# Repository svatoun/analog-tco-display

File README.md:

# analog-tco-display

Projekt se skládá z 2 částí: Analogové TCO a Zobrazovač obsazení

## Analogové TCO
**TCO je ovladač ANALOGOVÉHO kolejiště do ovládacího pultu**, pracuje s tlačítky (spínači) nebo přepínači. Čte stav tlačítek, sleduje změny a pomocí sběrnice RS485 odesílá jednotlivým výkonným zařízením pod kolejištěm. Sběrnice nahrazuje samostatné spínací / povelové vodiče vedoucí z pultu k jednotlivým servům, přestavníkům apod. TCO si vystačí se 3 vodiči (U+, U- a GND) a dokáže po nich přenést velké libovolné množství povelů.

Bežné "analogově řízené" kolejiště využívá jednoduchého spínání, tedy na každé zařízení (přestavník, lampa, světlo návěstidla atd) padne jeden vodič. Jejich množství může lehce vyčerpat vodiče v kabelu propojující ovládací panel s kolejištěm.

**POZOR** jedná se o ovládání ANALOGOVÉHO kolejiště, u digitálního kolejiště pomocí _XPressNet_ je pro komunikaci s centrálou použitá sicestejná kabeláž ale **jiný, standardizovaný, protokol** ! Komunikace a možnosti tohoto "analogového TCO" v žádném případě nedosahuje robustnosti a šíře protokolu XpressNet nebo LocoNet.

TCO se **konfiguruje** pomocí integrovaného USB portu v Arduinu, zapojeného do PC. 

Více viz [Analogové TCO](http://cs.ttodbocna.wikia.com/wiki/Analog_TCO)

## Zobrazení obsazení
Skládá se z několika částí:
- Proudové detektory obsazení uzpůsobené pro analogový provoz
- Enkodér detektorů pro sběrnici S88 (stejná jako se používá u digitalních kolejišť)
- Zobrazovací jednotka v ovládacím pultu
Umožňuje přenášet až 128 detekovaných úseků a zobrazovat jejich stav na ovládacím pultu. Umožňuje také do přenášených dat zapojit jiný tzp detektorů, 
např. jazýčková relé, optické senzory atd. 

Podrobnější popis bude doplněn.

## Celková "architektura"
Jak spolu spolupracují TCO, Display, proudove detektory atd atd je [vysvětleno ve Wiki](http://cs.ttodbocna.wikia.com/wiki/Architektura_Analog)

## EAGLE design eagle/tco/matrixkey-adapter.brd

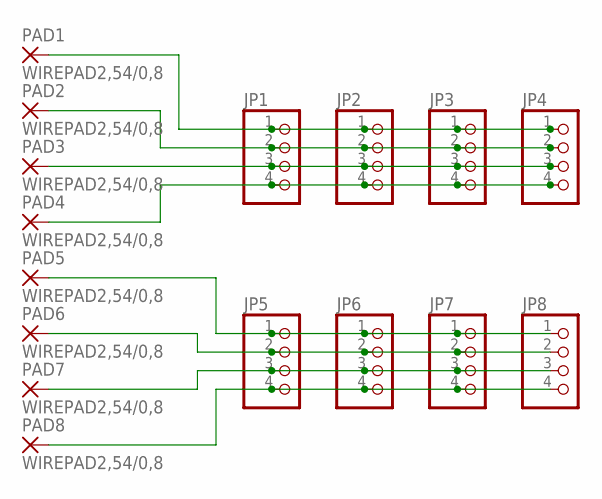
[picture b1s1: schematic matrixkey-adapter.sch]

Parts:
JP1, JP2, JP3, JP4, JP5, JP6, JP7, JP8: PINHD-1X4; 1X04
PAD1, PAD2, PAD3, PAD4, PAD5, PAD6, PAD7, PAD8: WIREPAD2,54/0,8; 2,54/0,8

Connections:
unnamed: JP1.1, JP2.1, JP3.1, JP4.1, PAD1.1
unnamed: JP1.2, JP2.2, JP3.2, JP4.2, PAD2.1
unnamed: JP1.3, JP2.3, JP3.3, JP4.3, PAD3.1
unnamed: JP1.4, JP2.4, JP3.4, JP4.4, PAD4.1
unnamed: JP5.1, JP6.1, JP7.1, JP8.1, PAD5.1
unnamed: JP5.2, JP6.2, JP7.2, JP8.2, PAD6.1
unnamed: JP5.3, JP6.3, JP7.3, JP8.3, PAD7.1
unnamed: JP5.4, JP6.4, JP7.4, JP8.4, PAD8.1

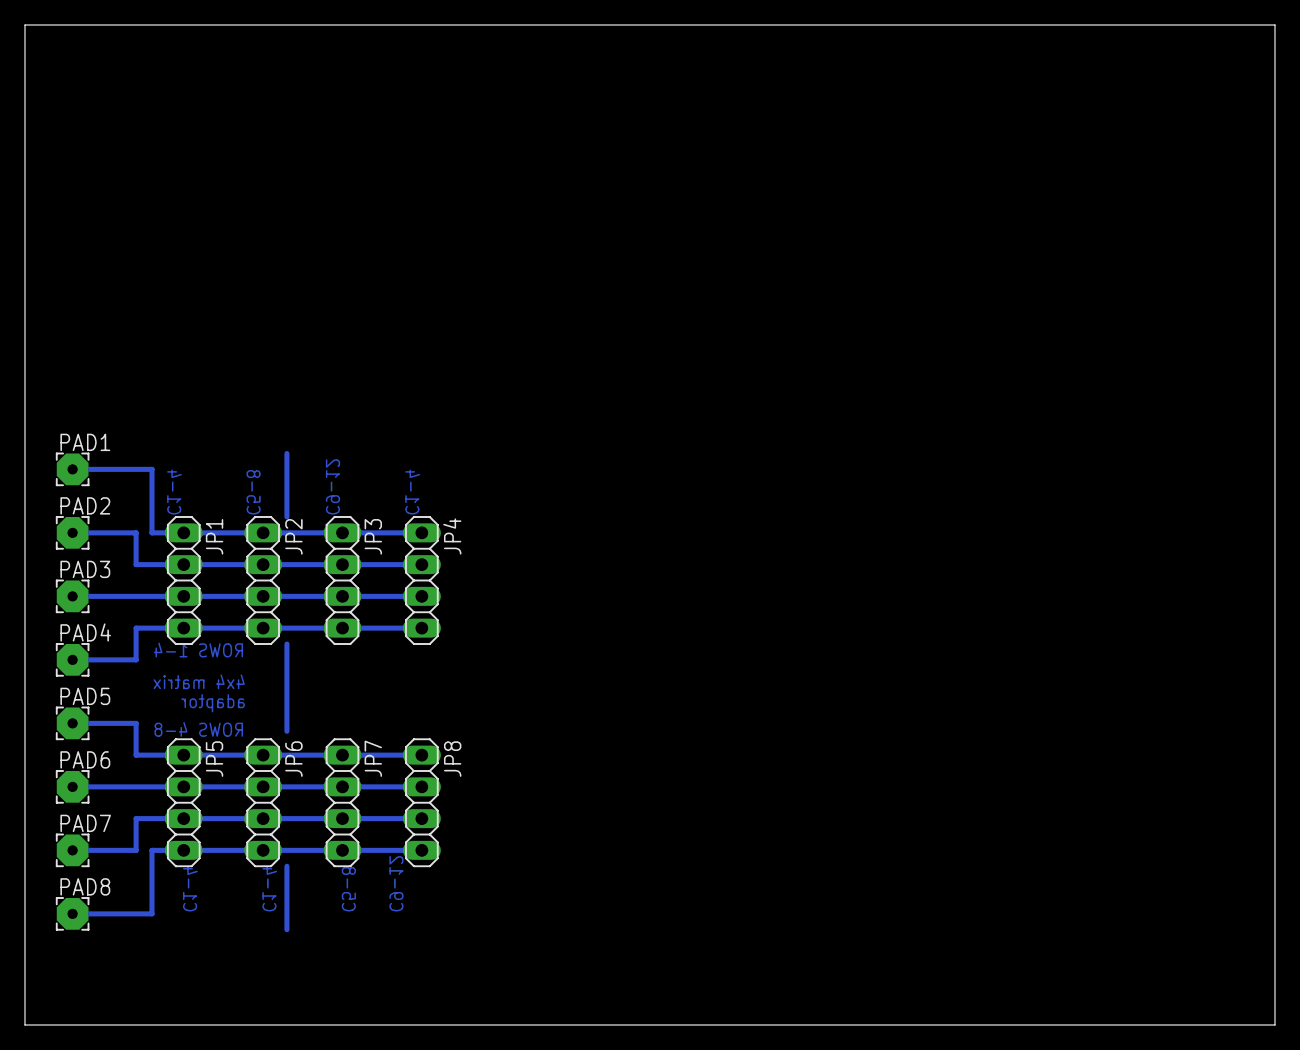
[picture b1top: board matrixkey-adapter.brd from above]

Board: 2 copper layers, 100.0 x 80.0 mm, 16 parts (0 on the bottom side), 8 nets.

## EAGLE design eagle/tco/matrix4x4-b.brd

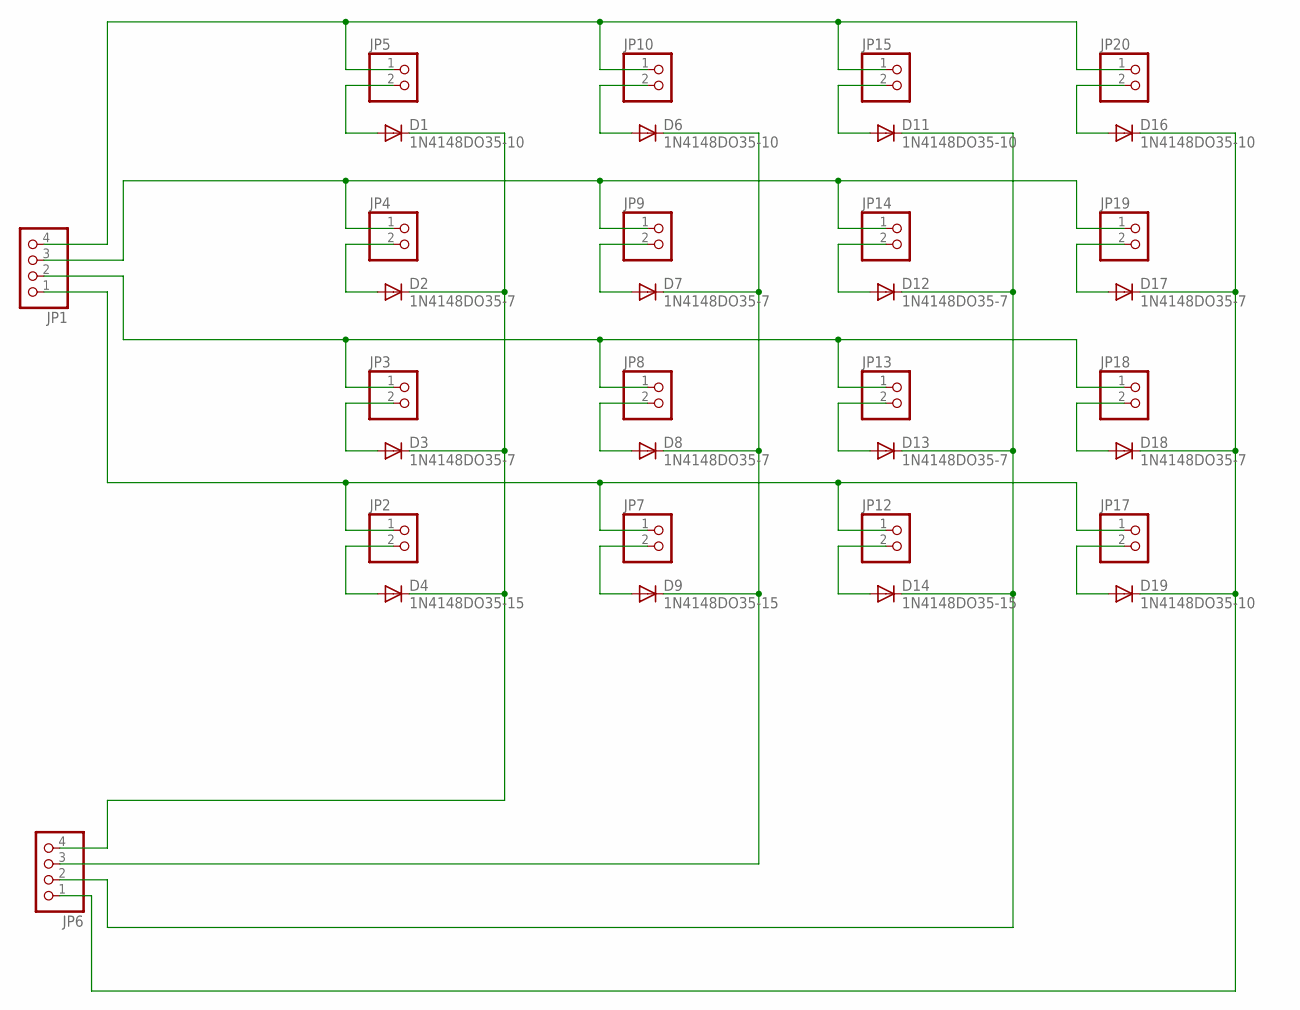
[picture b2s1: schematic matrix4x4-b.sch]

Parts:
D1, D6, D11, D16, D19: 1N4148DO35-10; DO35-10
D2, D3, D7, D8, D12, D13, D17, D18: 1N4148DO35-7; DO35-7
D4, D9, D14: 1N4148DO35-15; DO35-10
JP1, JP6: PINHD-1X4; 1X04
JP2, JP3, JP4, JP5, JP7, JP8, JP9, JP10, JP12, JP13, JP14, JP15, JP17, JP18, JP19, JP20: PINHD-1X2; 1X02

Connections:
unnamed: JP1.1, JP2.1, JP7.1, JP12.1, JP17.1
unnamed: JP1.2, JP3.1, JP8.1, JP13.1, JP18.1
unnamed: JP1.3, JP4.1, JP9.1, JP14.1, JP19.1
unnamed: JP1.4, JP5.1, JP10.1, JP15.1, JP20.1
unnamed: D1.A, JP5.2
unnamed: D2.A, JP4.2
unnamed: D4.A, JP2.2
unnamed: D1.C, D2.C, D3.C, D4.C, JP6.4
unnamed: D6.C, D7.C, D8.C, D9.C, JP6.3
unnamed: D11.C, D12.C, D13.C, D14.C, JP6.2
unnamed: D16.C, D17.C, D18.C, D19.C, JP6.1
unnamed: D6.A, JP10.2
unnamed: D7.A, JP9.2
unnamed: D9.A, JP7.2
unnamed: D3.A, JP3.2
unnamed: D8.A, JP8.2
unnamed: D13.A, JP13.2
unnamed: D18.A, JP18.2
unnamed: D11.A, JP15.2
unnamed: D12.A, JP14.2
unnamed: D14.A, JP12.2
unnamed: D16.A, JP20.2
unnamed: D17.A, JP19.2
unnamed: D19.A, JP17.2

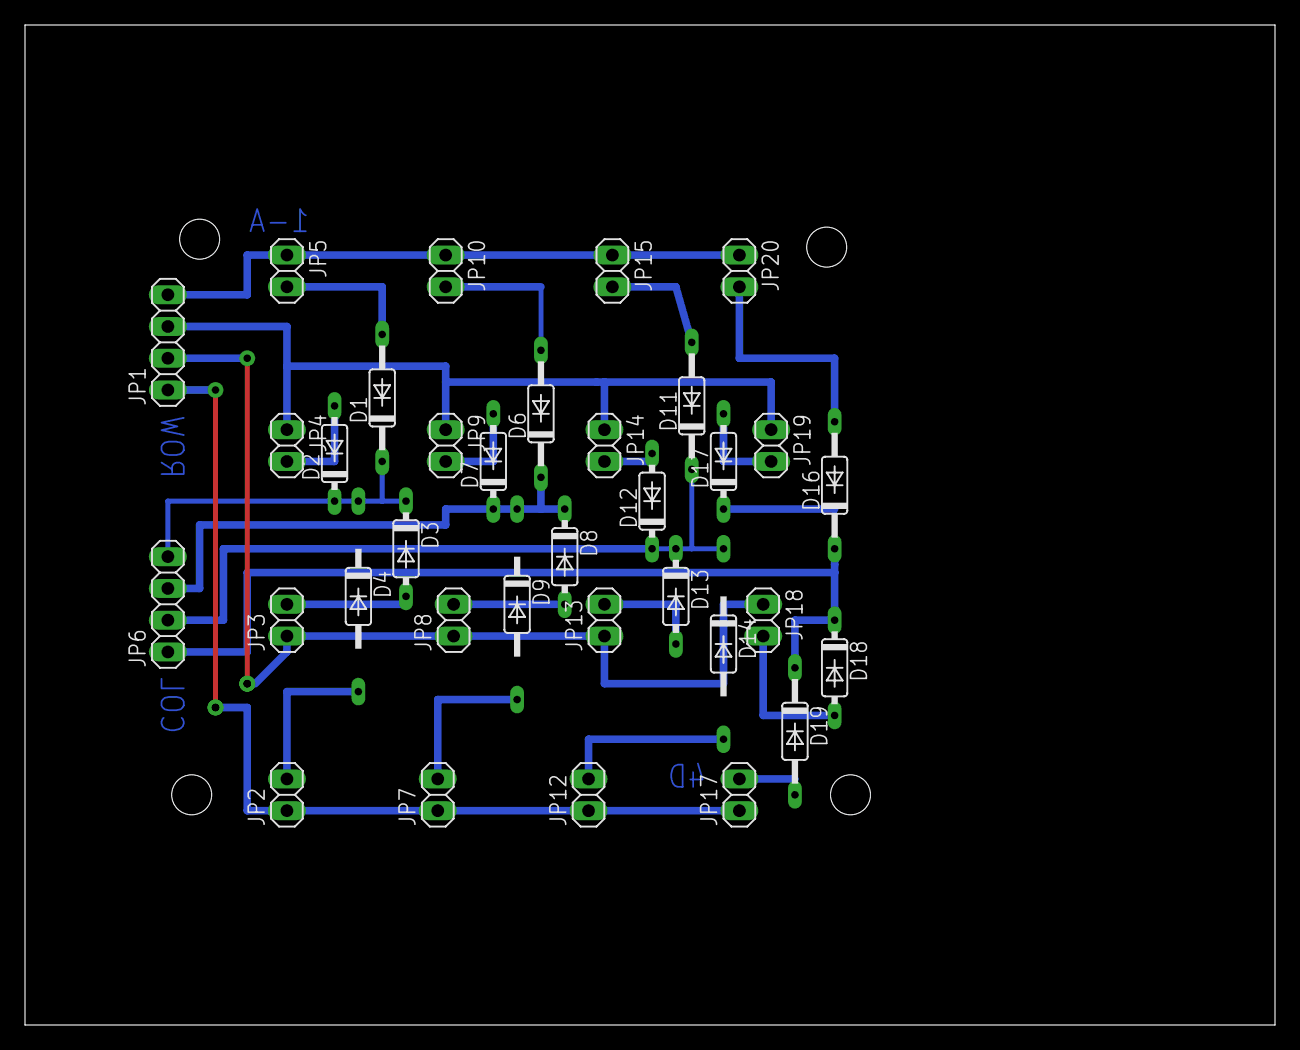
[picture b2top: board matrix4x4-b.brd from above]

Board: 2 copper layers, 100.0 x 80.0 mm, 34 parts (0 on the bottom side), 24 nets.

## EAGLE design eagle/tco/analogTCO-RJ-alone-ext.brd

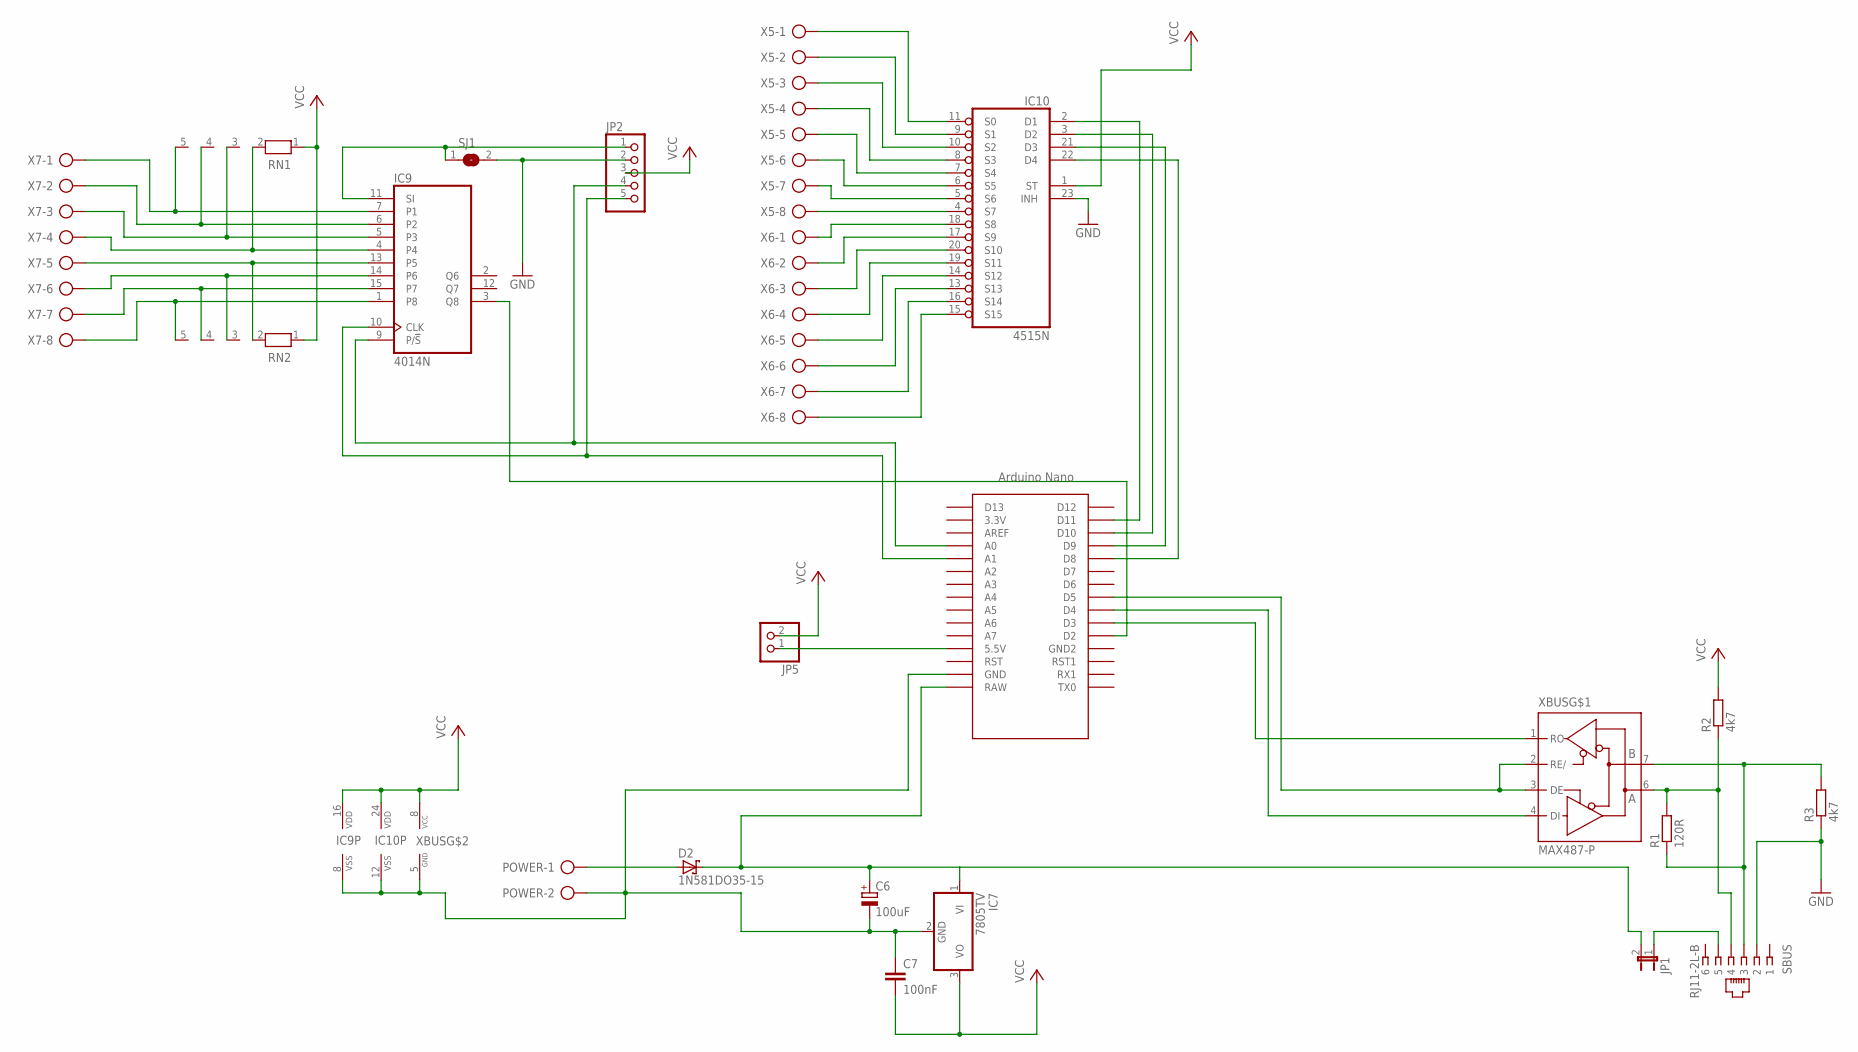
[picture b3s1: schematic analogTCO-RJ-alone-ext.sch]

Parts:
C6: 100uF; E2,5-6
C7: 100nF; C025-025X050
D2: 1N581DO35-15; DO35-10
IC7: 7805TV; TO220V
IC9: 4014N; DIL16
IC10: 4515N; DIL24-6
JP1: JP1E; JP1
JP2: PINHD-1X5; 1X05
JP5: PINHD-1X2; 1X02
POWER: AK500/2
R1: 120R; 0207/12
R2, R3: 4k7; 0207/12
RN1, RN2: RN04; RN-5
SBUS: RJ11-2L-B; RJ11-NO_SHIELD
SJ1: SJ
U$1: NANO
X5, X6, X7: AK500/8
XBUS: MAX487-P; DIL08

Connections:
+12V: C6.+, D2.C, IC7.1 (VI), JP1.2, U$1.RAW
GND: C6.-, C7.1, IC7.2 (GND), IC9.8 (VSS), IC10.12 (VSS), IC10.23 (INH), JP2.2, POWER.2, R3.1, SBUS.2, SJ1.2, U$1.GND, XBUS.5 (GND)
unnamed: U$1.D5, XBUS.2 (RE/), XBUS.3 (DE)
unnamed: U$1.D3, XBUS.1 (RO)
unnamed: U$1.D4, XBUS.4 (DI)
unnamed: R1.2, R2.1, SBUS.4, XBUS.6 (A)
unnamed: R1.1, R3.2, SBUS.3, XBUS.7 (B)
unnamed: JP5.1, U$1.5V (5.5V)
unnamed: JP1.1, SBUS.5
unnamed: IC9.11 (SI), JP2.1, SJ1.1
unnamed: IC10.3 (D2), U$1.D10
unnamed: IC10.2 (D1), U$1.D11
unnamed: IC9.9 (P/!S), JP2.4, U$1.A0
unnamed: IC9.10 (CLK), JP2.5, U$1.A1
unnamed: IC9.3 (Q8), U$1.D2
unnamed: IC10.11 (S0), X5.1
unnamed: IC10.9 (S1), X5.2
unnamed: IC10.10 (S2), X5.3
unnamed: IC10.8 (S3), X5.4
unnamed: IC10.7 (S4), X5.5
unnamed: IC10.6 (S5), X5.6
unnamed: IC10.5 (S6), X5.7
unnamed: IC10.4 (S7), X5.8
unnamed: IC10.18 (S8), X6.1
unnamed: IC10.17 (S9), X6.2
unnamed: IC10.20 (S10), X6.3
unnamed: IC10.19 (S11), X6.4
unnamed: IC10.14 (S12), X6.5
unnamed: IC10.13 (S13), X6.6
unnamed: IC10.16 (S14), X6.7
unnamed: IC10.15 (S15), X6.8
unnamed: IC9.7 (P1), RN1.5, X7.1
unnamed: IC9.6 (P2), RN1.4, X7.2
unnamed: IC9.5 (P3), RN1.3, X7.3
unnamed: IC9.4, RN1.2, X7.4
unnamed: IC9.13 (P5), RN2.2, X7.5
unnamed: IC9.14 (P6), RN2.3, X7.6
unnamed: IC9.15 (P7), RN2.4, X7.7
unnamed: IC9.1 (P8), RN2.5, X7.8
unnamed: IC10.21 (D3), U$1.D9
unnamed: IC10.22 (D4), U$1.D8
unnamed: D2.A, POWER.1
VCC: C7.2, IC7.3 (VO), IC9.16 (VDD), IC10.1 (ST), IC10.24 (VDD), JP2.3, JP5.2, R2.2, RN1.1, RN2.1, XBUS.8 (VCC)

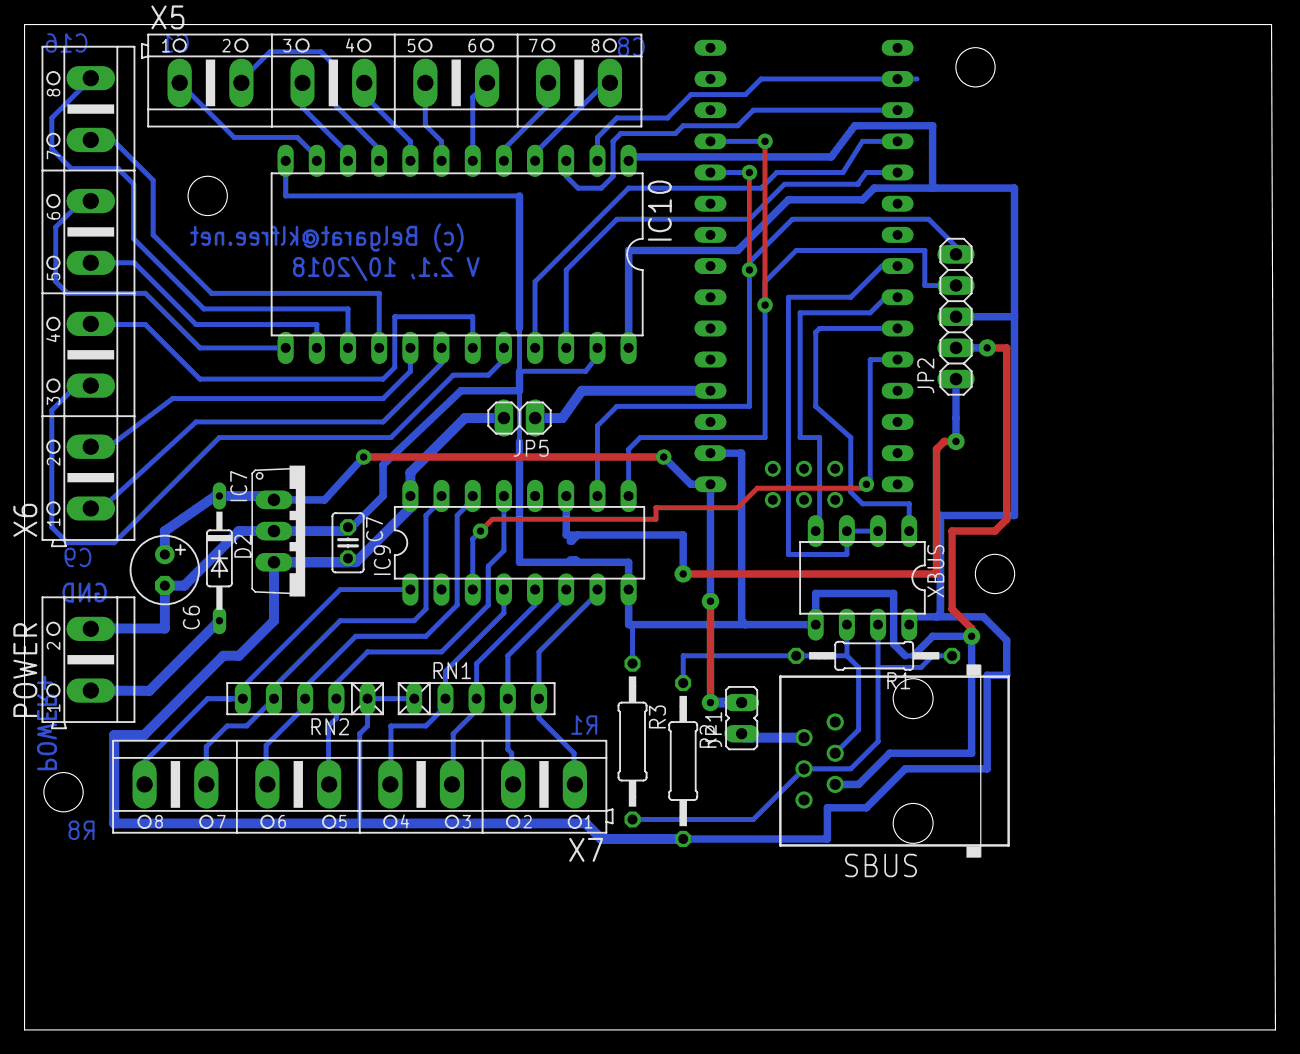
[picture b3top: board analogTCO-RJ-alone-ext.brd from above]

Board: 2 copper layers, 101.9 x 81.9 mm, 22 parts (1 on the bottom side), 43 nets.

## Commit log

2018-08-16 Prvni verze
2018-09-05 Work in progress
2018-09-16 Funkcni verze
2018-09-16 Samostatny display
2018-09-16 Oprava bitoveho posunu S88, oprava detekce trakcniho napeti
2018-09-16 Jen Komentare
2018-10-06 Bugfixes
2018-10-28 Nastaveni adresy
2018-10-29 Male opravy z psani dokumentace
2018-10-29 Spravna verze schematu
2018-10-29 Vycisteny zbytky, co patrily k S88 Display
2018-10-29 Pridana matice pro tlacitka s diodami; adapter pro matice do svorkovnice
